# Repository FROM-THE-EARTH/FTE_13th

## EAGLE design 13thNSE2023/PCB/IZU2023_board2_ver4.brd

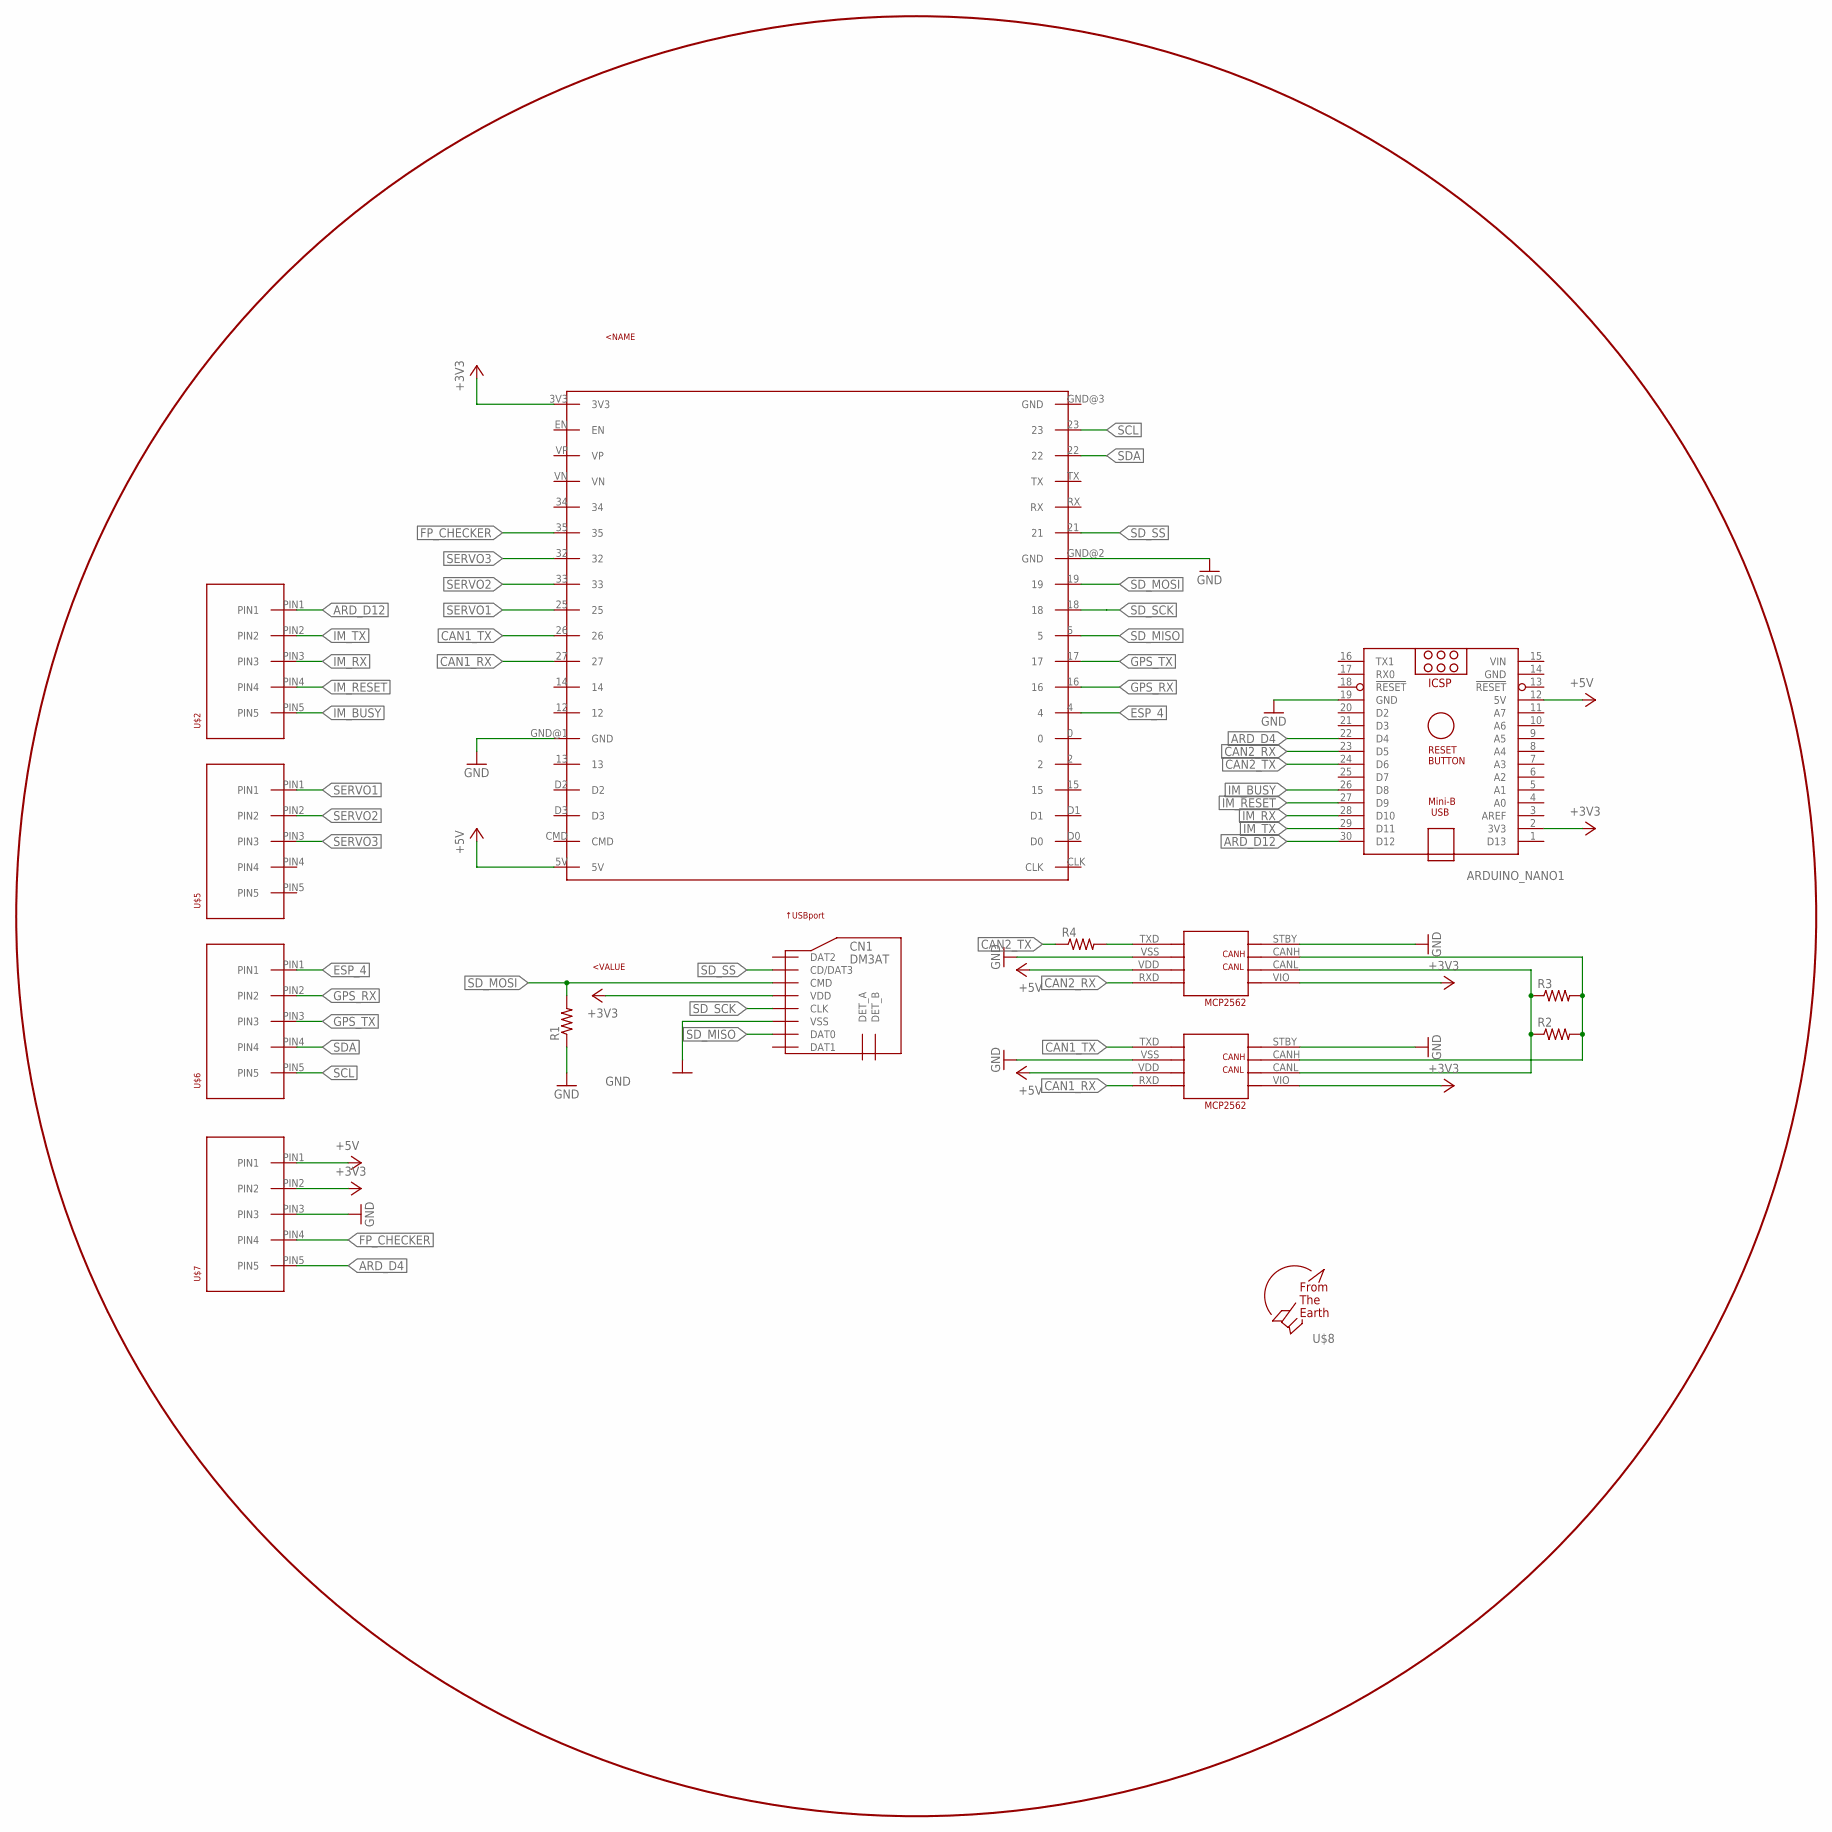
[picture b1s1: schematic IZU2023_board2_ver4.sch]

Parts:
ARDUINO_NANO1: ARDUINO_NANO
CN1: DM3AT
R1, R2, R3, R4: R-US_0204/7; 0204/7
U$1: ESP32-DEVKITC
U$2, U$5, U$6, U$7: 5PIN
U$3, U$4: MCP2562
U$8: F.T.E.LOGO; LOGO

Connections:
+3V3: ARDUINO_NANO1.2 (3V3), CN1.VDD, U$1.3V3, U$3.VIO, U$4.VIO, U$7.PIN2
+5V: ARDUINO_NANO1.12 (5V), U$1.5V, U$3.VDD, U$4.VDD, U$7.PIN1
ARD_D4: ARDUINO_NANO1.22 (D4), U$7.PIN5
ARD_D12: ARDUINO_NANO1.30 (D12), U$2.PIN1
CAN1_RX: U$1.27, U$3.RXD
CAN1_TX: U$1.26, U$3.TXD
CAN2_RX: ARDUINO_NANO1.23 (D5), U$4.RXD
CAN2_TX: ARDUINO_NANO1.24 (D6), R4.1
ESP_4: U$1.4, U$6.PIN1
FP_CHECKER: U$1.35, U$7.PIN4
GND: ARDUINO_NANO1.14 (GND), ARDUINO_NANO1.19 (GND), CN1.VSS, R1.1, U$1.GND@1 (GND), U$1.GND@2 (GND), U$3.STBY, U$3.VSS, U$4.STBY, U$4.VSS, U$7.PIN3
GPS_RX: U$1.16, U$6.PIN2
GPS_TX: U$1.17, U$6.PIN3
IM_BUSY: ARDUINO_NANO1.26 (D8), U$2.PIN5
IM_RESET: ARDUINO_NANO1.27 (D9), U$2.PIN4
IM_RX: ARDUINO_NANO1.28 (D10), U$2.PIN3
IM_TX: ARDUINO_NANO1.29 (D11), U$2.PIN2
unnamed: R4.2, U$4.TXD
unnamed: R2.1, R3.1, U$3.CANL, U$4.CANL
unnamed: R2.2, R3.2, U$3.CANH, U$4.CANH
SCL: U$1.23, U$6.PIN5
SDA: U$1.22, U$6.PIN4
SD_MISO: CN1.DAT0, U$1.5
SD_MOSI: CN1.CMD, R1.2, U$1.19
SD_SCK: CN1.CLK, U$1.18
SD_SS: CN1.CD/DAT3, U$1.21
SERVO1: U$1.25, U$5.PIN1
SERVO2: U$1.33, U$5.PIN2
SERVO3: U$1.32, U$5.PIN3
VIN: ARDUINO_NANO1.15 (VIN)

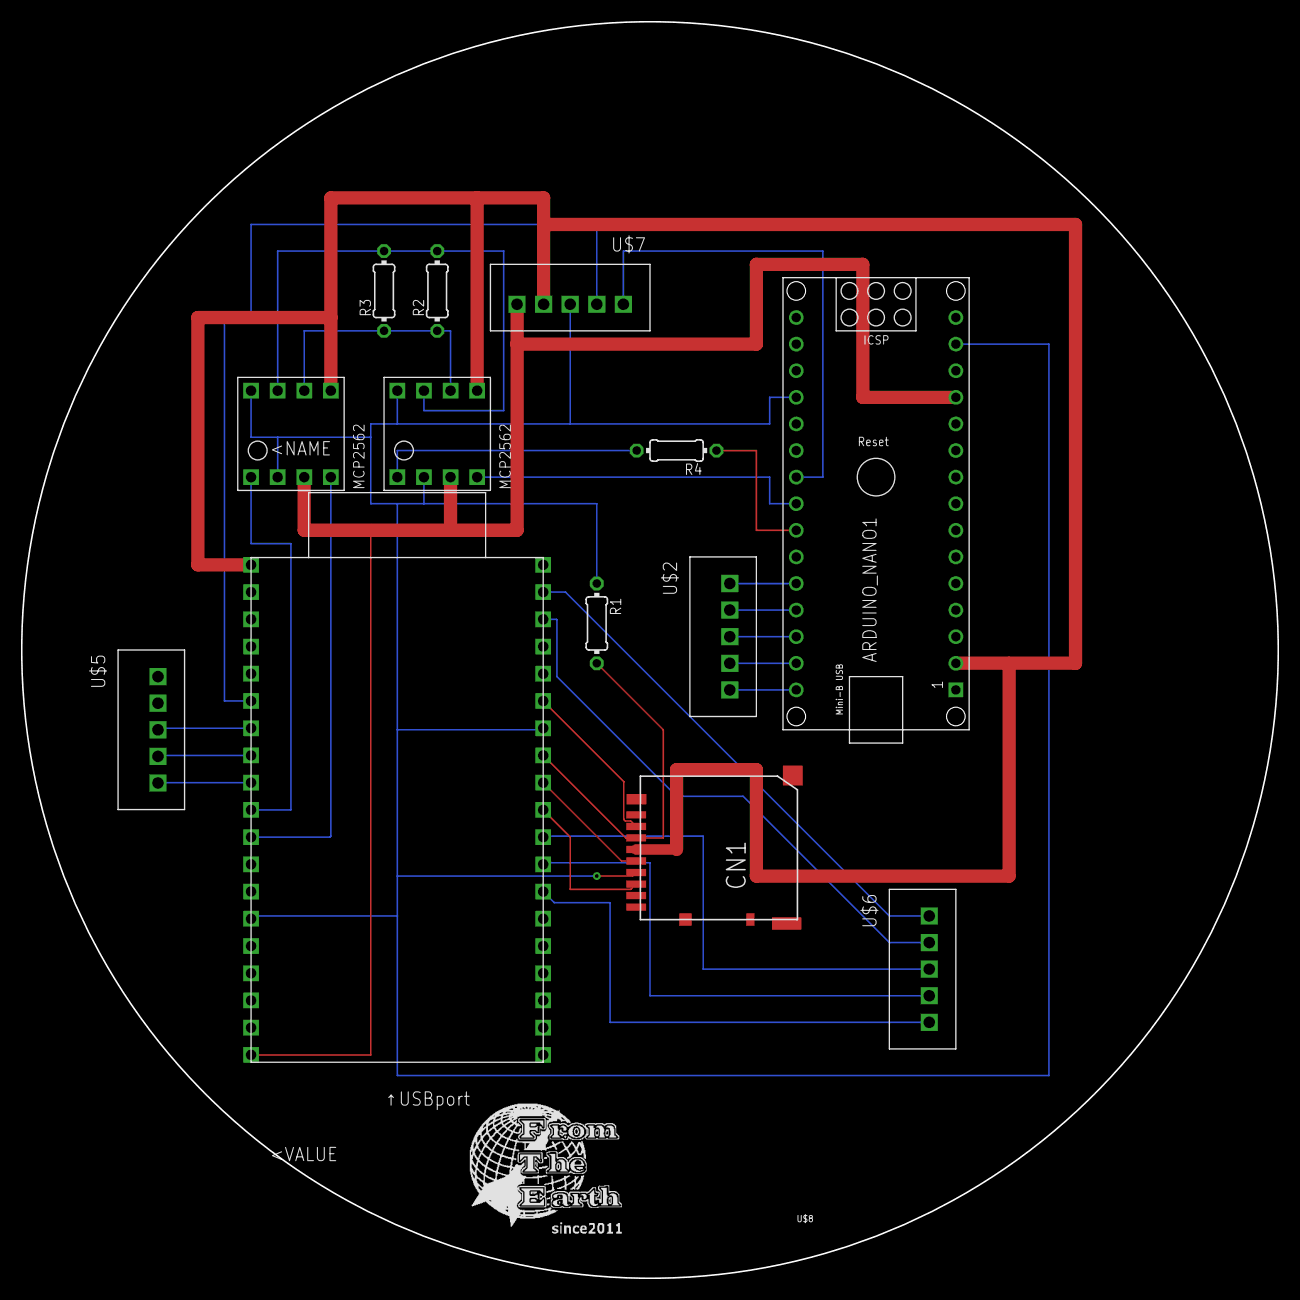
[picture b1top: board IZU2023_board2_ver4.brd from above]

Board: 2 copper layers, 120.0 x 120.0 mm, 14 parts (0 on the bottom side), 29 nets.

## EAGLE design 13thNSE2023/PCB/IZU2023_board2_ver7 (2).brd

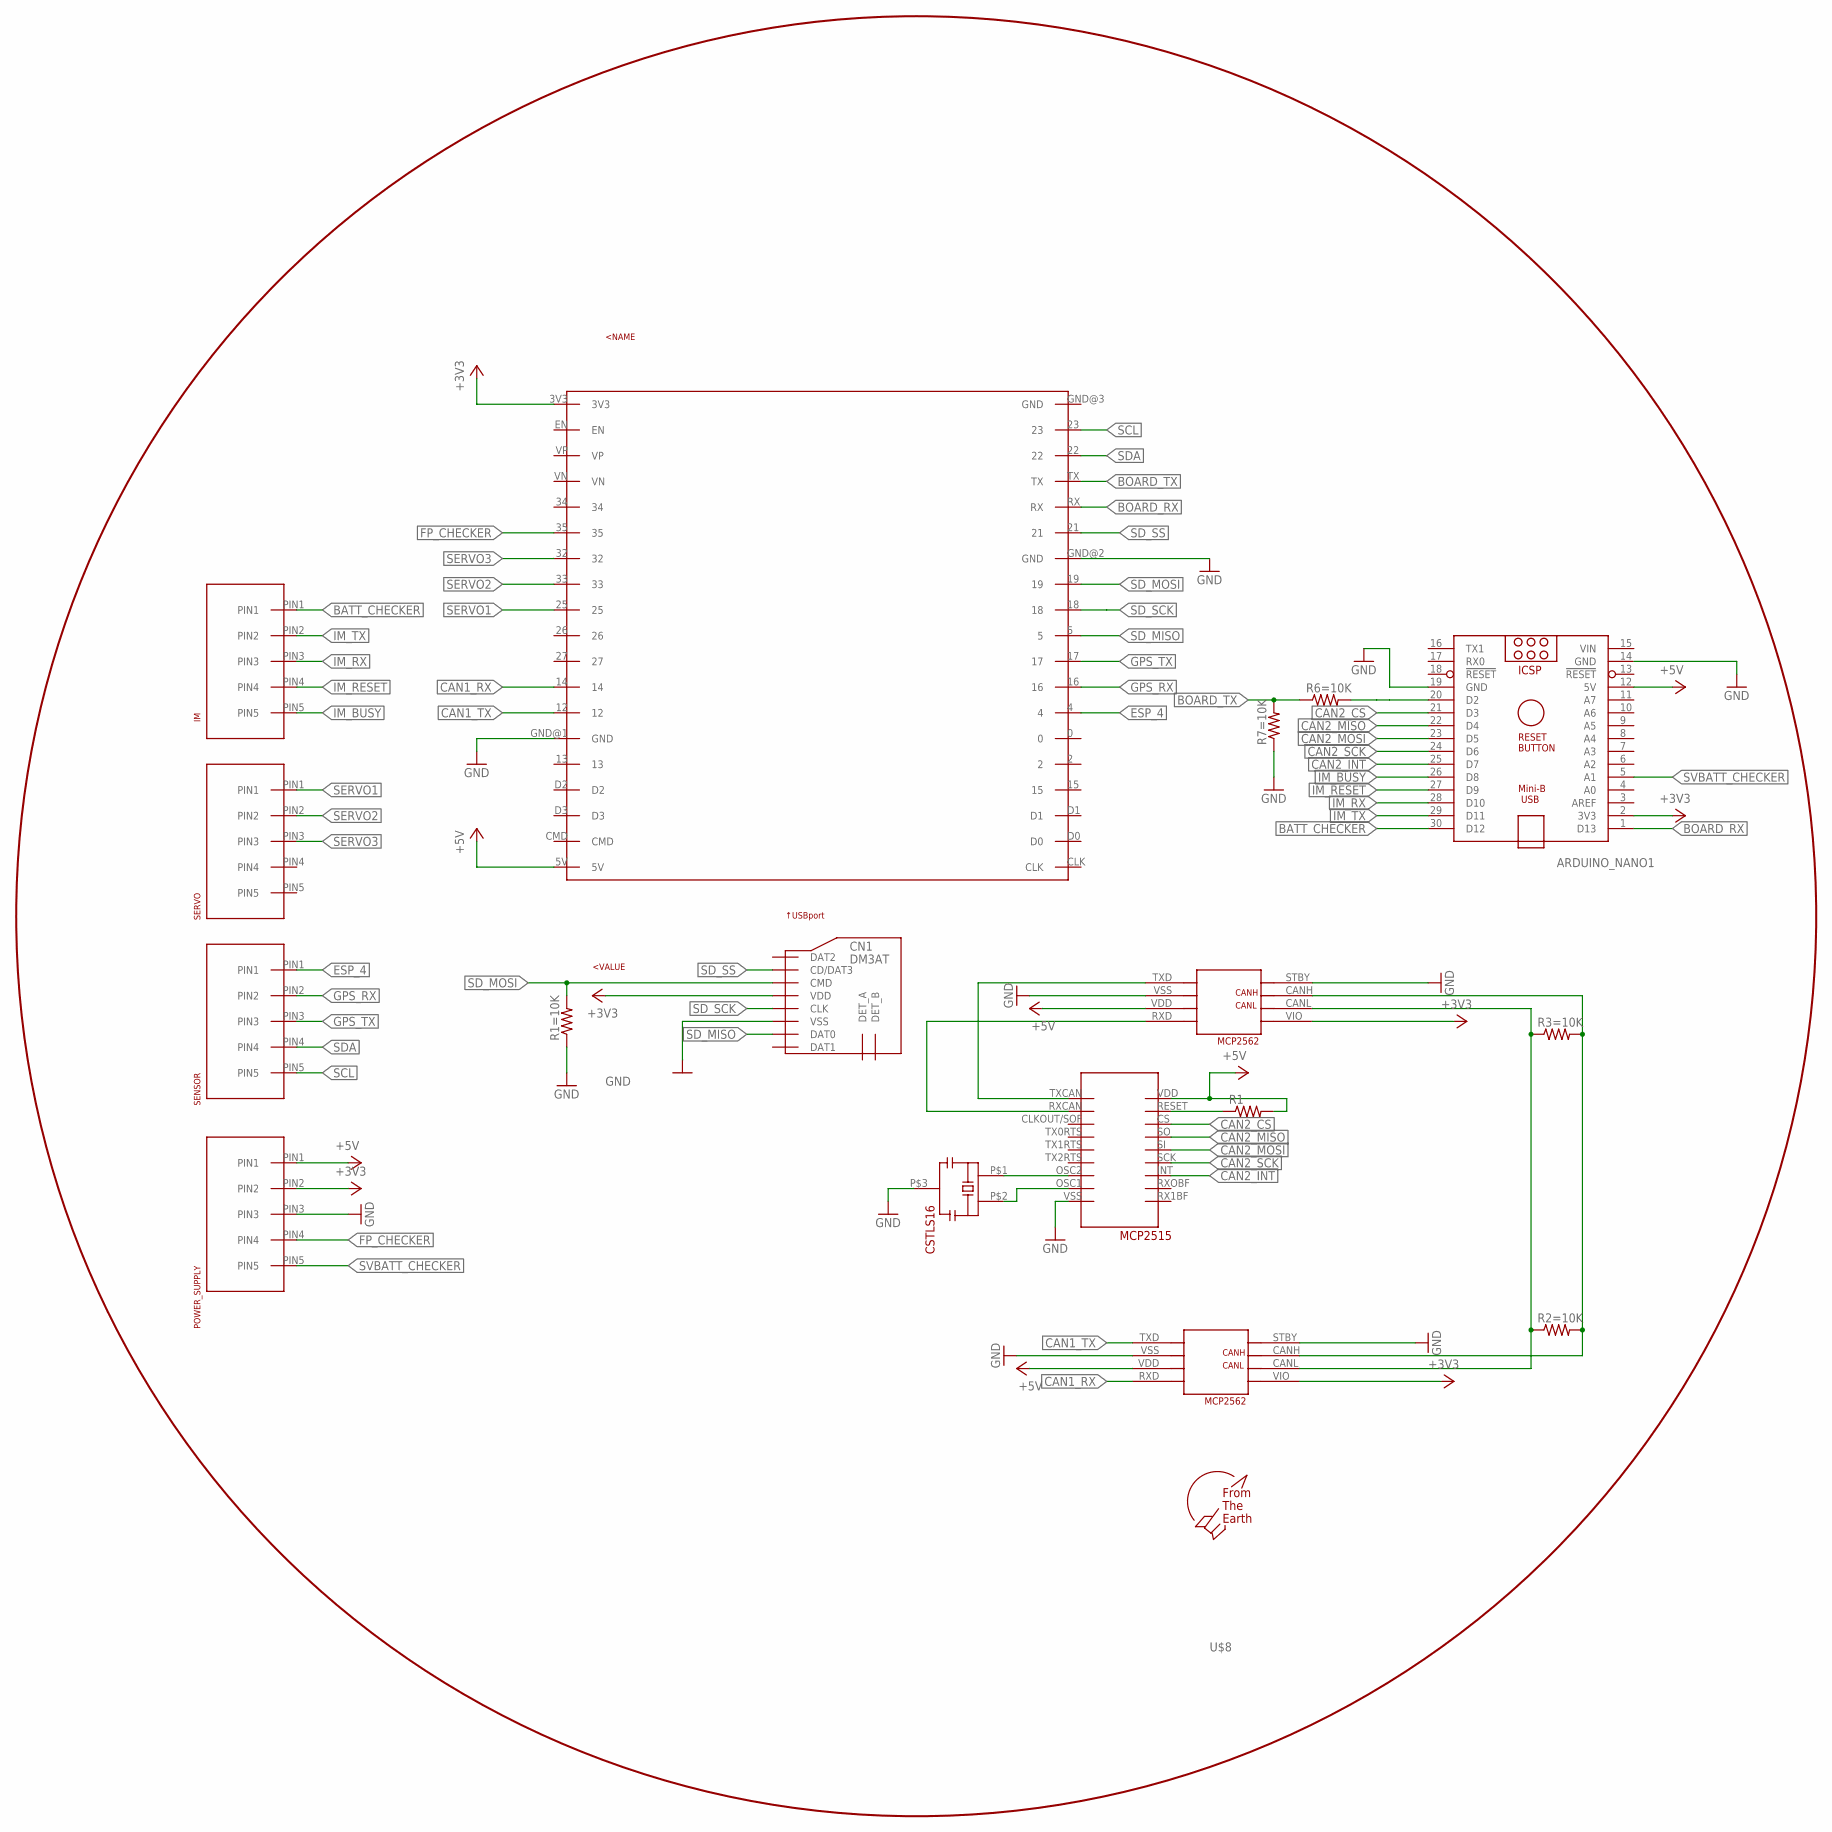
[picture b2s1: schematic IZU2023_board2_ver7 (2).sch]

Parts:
ARDUINO_NANO1: ARDUINO_NANO
CN1: DM3AT
IM: 5PIN
POWER_SUPPLY: 5PIN
R1, R1=10K, R2=10K, R3=10K, R6=10K, R7=10K: R-US_0204/7; 0204/7
SENSOR: 5PIN
SERVO: 5PIN
U$1: ESP32-DEVKITC
U$2: MCP2515
U$3, U$4: MCP2562
U$5: CSTLS16
U$8: F.T.E.LOGO; LOGO

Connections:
+3V3: ARDUINO_NANO1.2 (3V3), CN1.VDD, POWER_SUPPLY.PIN2, U$1.3V3, U$3.VIO, U$4.VIO
+5V: ARDUINO_NANO1.12 (5V), POWER_SUPPLY.PIN1, R1.2, U$1.5V, U$2.VDD, U$3.VDD, U$4.VDD
BATT_CHECKER: ARDUINO_NANO1.30 (D12), IM.PIN1
BOARD_RX: ARDUINO_NANO1.1 (D13), U$1.RX
BOARD_TX: R6=10K.1, R7=10K.2, U$1.TX
CAN1_RX: U$1.14, U$3.RXD
CAN1_TX: U$1.12, U$3.TXD
CAN2_CS: ARDUINO_NANO1.21 (D3), U$2.CS
CAN2_INT: ARDUINO_NANO1.25 (D7), U$2.INT
CAN2_MISO: ARDUINO_NANO1.22 (D4), U$2.SO
CAN2_MOSI: ARDUINO_NANO1.23 (D5), U$2.SI
CAN2_SCK: ARDUINO_NANO1.24 (D6), U$2.SCK
ESP_4: SENSOR.PIN1, U$1.4
FP_CHECKER: POWER_SUPPLY.PIN4, U$1.35
GND: ARDUINO_NANO1.14 (GND), ARDUINO_NANO1.19 (GND), CN1.VSS, POWER_SUPPLY.PIN3, R1=10K.1, R7=10K.1, U$1.GND@1 (GND), U$1.GND@2 (GND), U$2.VSS, U$3.STBY, U$3.VSS, U$4.STBY, U$4.VSS, U$5.P$3
GPS_RX: SENSOR.PIN2, U$1.16
GPS_TX: SENSOR.PIN3, U$1.17
IM_BUSY: ARDUINO_NANO1.26 (D8), IM.PIN5
IM_RESET: ARDUINO_NANO1.27 (D9), IM.PIN4
IM_RX: ARDUINO_NANO1.28 (D10), IM.PIN3
IM_TX: ARDUINO_NANO1.29 (D11), IM.PIN2
unnamed: U$2.TXCAN, U$4.TXD
unnamed: ARDUINO_NANO1.20 (D2), R6=10K.2
unnamed: R2=10K.1, R3=10K.1, U$3.CANL, U$4.CANL
unnamed: R2=10K.2, R3=10K.2, U$3.CANH, U$4.CANH
unnamed: U$2.RXCAN, U$4.RXD
unnamed: U$2.OSC2, U$5.P$1
unnamed: U$2.OSC1, U$5.P$2
unnamed: R1.1, U$2.RESET
SCL: SENSOR.PIN5, U$1.23
SDA: SENSOR.PIN4, U$1.22
SD_MISO: CN1.DAT0, U$1.5
SD_MOSI: CN1.CMD, R1=10K.2, U$1.19
SD_SCK: CN1.CLK, U$1.18
SD_SS: CN1.CD/DAT3, U$1.21
SERVO1: SERVO.PIN1, U$1.25
SERVO2: SERVO.PIN2, U$1.33
SERVO3: SERVO.PIN3, U$1.32
SVBATT_CHECKER: ARDUINO_NANO1.5 (A1), POWER_SUPPLY.PIN5
VIN: ARDUINO_NANO1.15 (VIN)

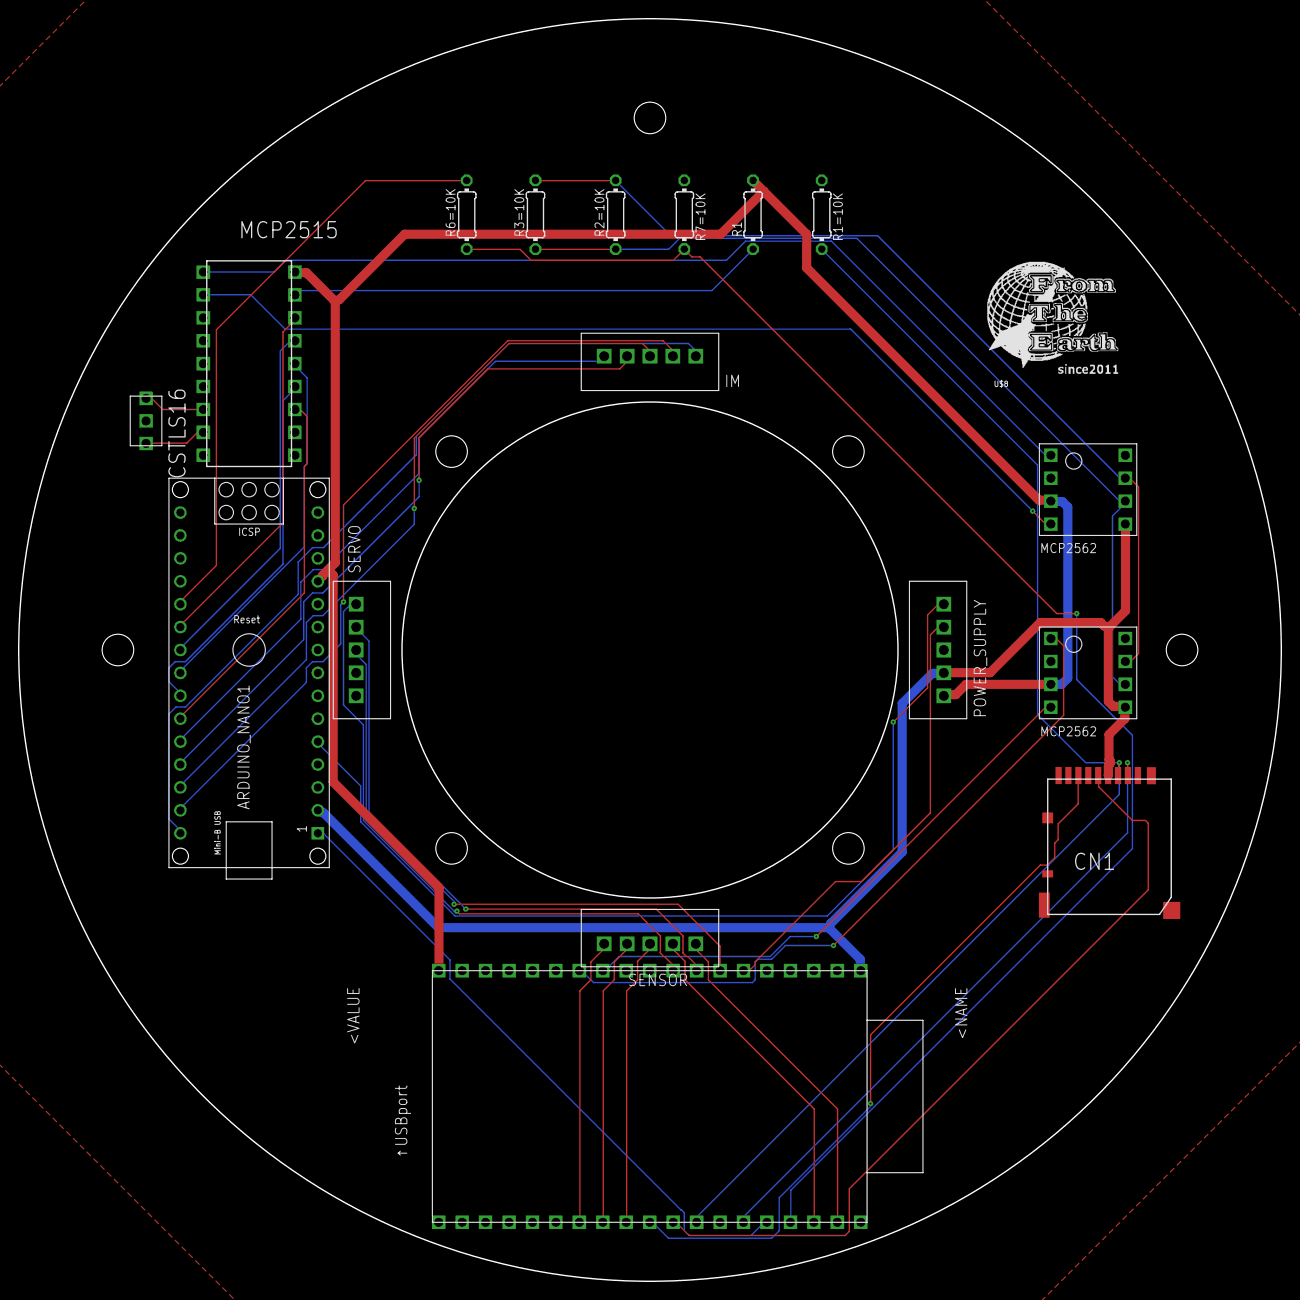
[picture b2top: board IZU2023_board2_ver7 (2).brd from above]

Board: 2 copper layers, 140.0 x 140.0 mm, 18 parts (0 on the bottom side), 39 nets.

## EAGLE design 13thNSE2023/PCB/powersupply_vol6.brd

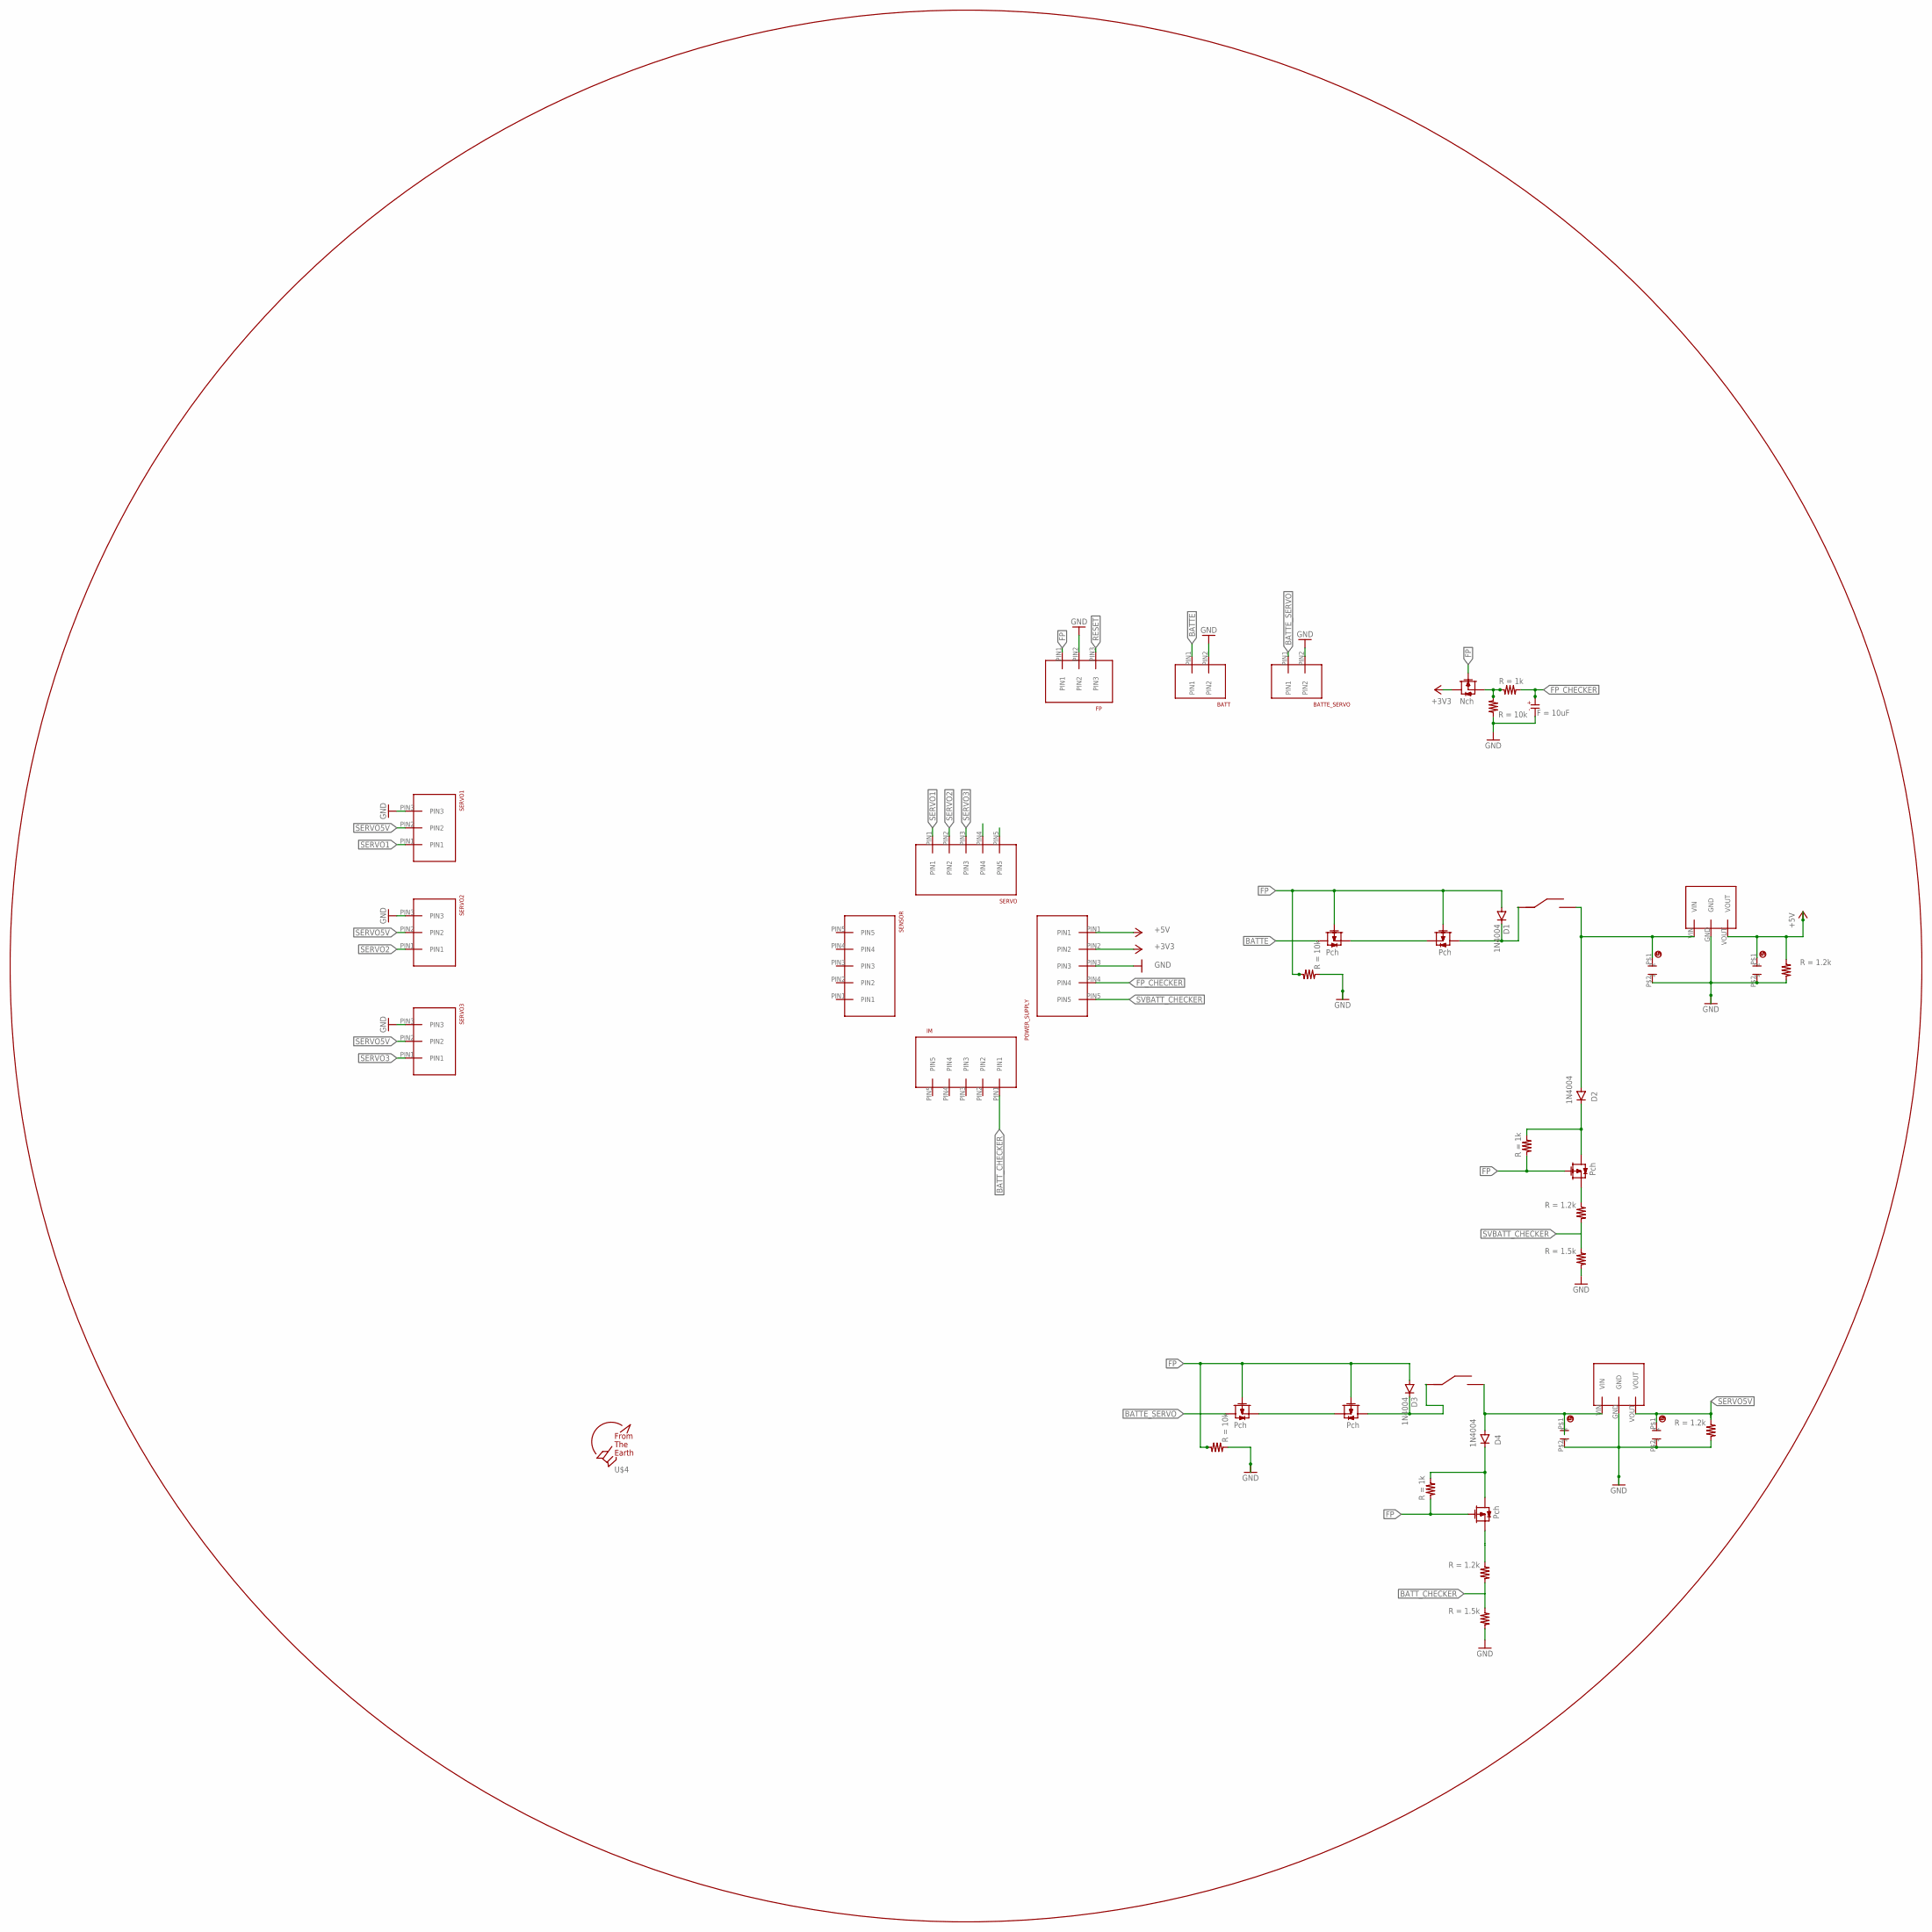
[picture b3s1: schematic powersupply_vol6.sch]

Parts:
BATT: 2PIN
BATTE_SERVO: 2PIN
C1: CAPACITOR-ELECTROLYTIC_1
CERAMIC_CAPACITOR3, CERAMIC_CAPACITOR4, CERAMIC_CAPACITOR5, CERAMIC_CAPACITOR6: CERAMIC_CAPACITOR
D1, D2, D3, D4: 1N4004; DO41-10
FP: 3PIN
IM: 5PIN
POWER_SUPPLY: 5PIN
R1, R4: 1.5k; REGISTER
R2, R3, R5, R6, R7, R8, R9, R10, R11, R12: RESISTER; REGISTER
SENSOR: 5PIN
SERVO: 5PIN
SERVO1, SERVO2, SERVO3: 3PIN
U$1, U$5, U$12, U$13, U$30, U$31: 2SJ681-PCH; 2SJ681
U$2, U$3: SLIDESWITCH
U$4: F.T.E.LOGO; LOGO
U$8: 2SK4017-NCH; 2SK4017
U$14, U$32: M78AR05-1

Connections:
+3V3: POWER_SUPPLY.PIN2, U$8.DRAIN
+5V: CERAMIC_CAPACITOR5.P$1 (1), POWER_SUPPLY.PIN1, R11.A, U$32.VOUT
BATTE: BATT.PIN1, U$30.DRAIN
BATTE_SERVO: BATTE_SERVO.PIN1, U$13.DRAIN
BATT_CHECKER: IM.PIN1, R1.A, R3.B
FP: D1.A, D3.A, FP.PIN1, R2.B, R5.B, R7.B, R8.B, U$1.GATE, U$5.GATE, U$8.GATE, U$12.GATE, U$13.GATE, U$30.GATE, U$31.GATE
FP_CHECKER: C1.KS, POWER_SUPPLY.PIN4, R10.A
GND: BATT.PIN2, BATTE_SERVO.PIN2, C1.AN, CERAMIC_CAPACITOR3.P$2 (2), CERAMIC_CAPACITOR4.P$2 (2), CERAMIC_CAPACITOR5.P$2 (2), CERAMIC_CAPACITOR6.P$2 (2), FP.PIN2, POWER_SUPPLY.PIN3, R1.B, R2.A, R4.B, R5.A, R9.A, R11.B, R12.B, SERVO1.PIN3, SERVO2.PIN3, SERVO3.PIN3, U$14.GND, U$32.GND
unnamed: D2.C, R7.A, U$1.DRAIN
unnamed: U$12.SOURCE, U$13.SOURCE
unnamed: R6.A, U$1.SOURCE
unnamed: D4.C, R8.A, U$5.DRAIN
unnamed: R9.B, R10.B, U$8.SOURCE
unnamed: CERAMIC_CAPACITOR4.P$1 (1), D4.A, U$3.C, U$14.VIN
unnamed: R3.A, U$5.SOURCE
unnamed: D1.C, U$2.A, U$31.DRAIN
unnamed: D3.C, U$3.A, U$12.DRAIN
unnamed: U$30.SOURCE, U$31.SOURCE
unnamed: CERAMIC_CAPACITOR6.P$1 (1), D2.A, U$2.C, U$32.VIN
RESET: FP.PIN3
SERVO1: SERVO.PIN1, SERVO1.PIN1
SERVO2: SERVO.PIN2, SERVO2.PIN1
SERVO3: SERVO.PIN3, SERVO3.PIN1
SERVO5V: CERAMIC_CAPACITOR3.P$1 (1), R12.A, SERVO1.PIN2, SERVO2.PIN2, SERVO3.PIN2, U$14.VOUT
SVBATT_CHECKER: POWER_SUPPLY.PIN5, R4.A, R6.B

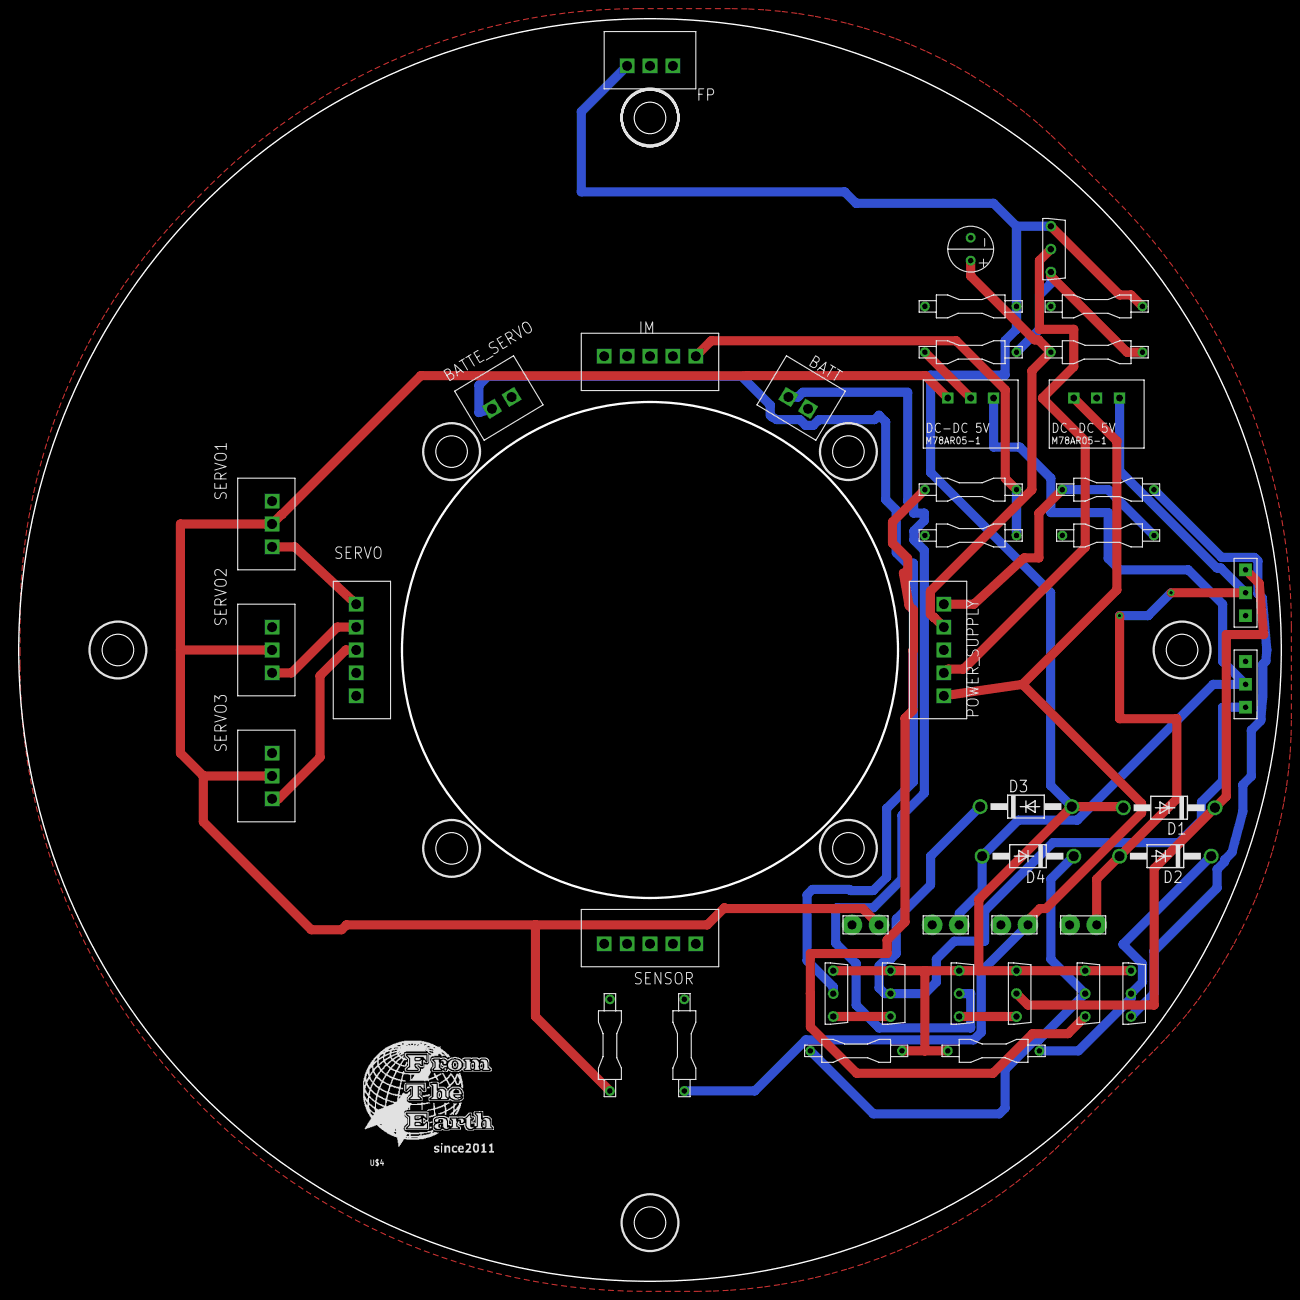
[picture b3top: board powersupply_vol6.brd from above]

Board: 2 copper layers, 140.0 x 140.0 mm, 43 parts (0 on the bottom side), 24 nets.

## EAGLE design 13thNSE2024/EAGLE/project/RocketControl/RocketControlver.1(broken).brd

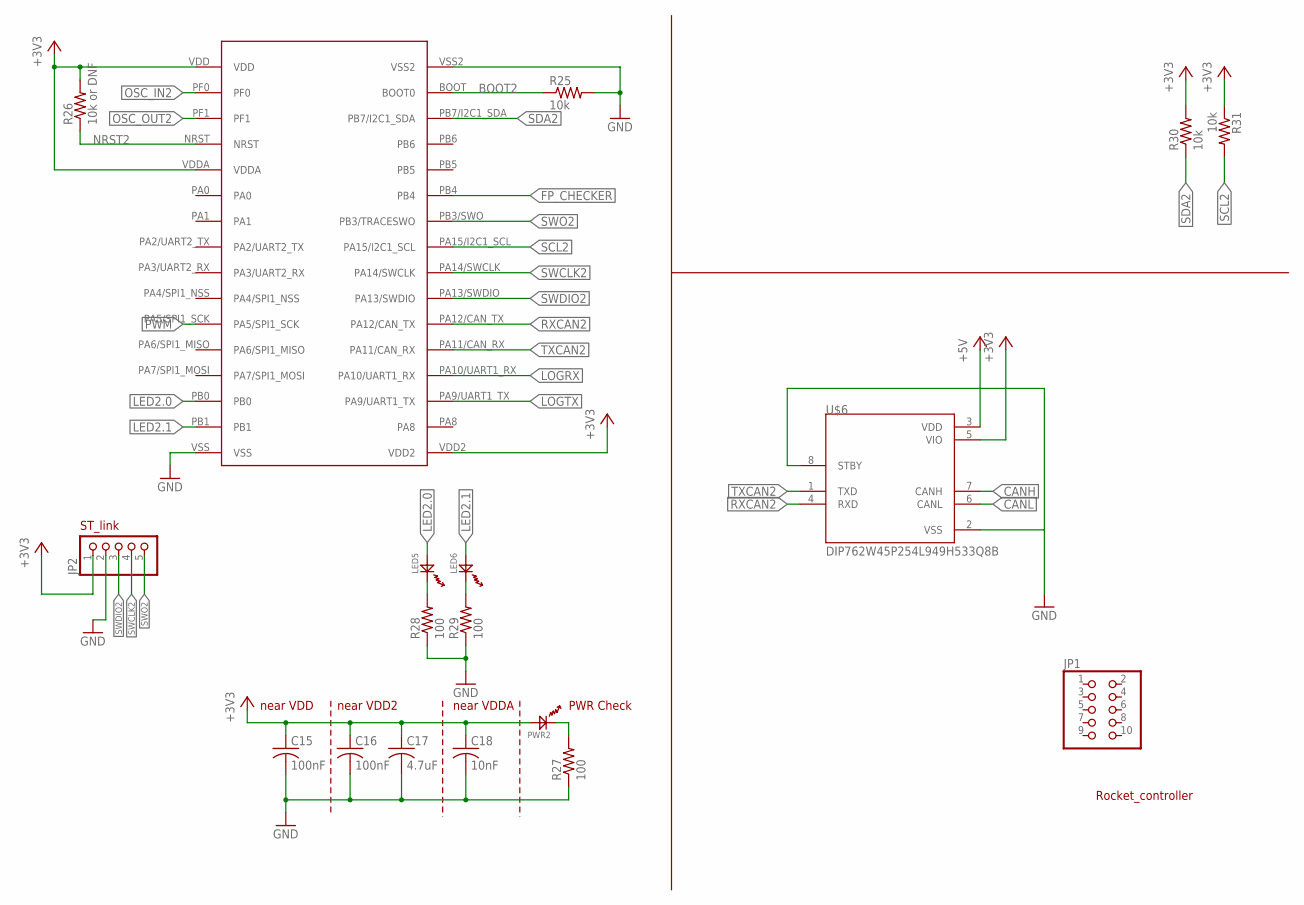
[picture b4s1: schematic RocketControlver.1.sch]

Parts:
C15, C16: 100nF; C1608
C17: 4.7uF; C1608
C18: 10nF; C1608
JP1: PINHD-2X5/90; 2X05/90
JP2: PINHD-1X5/90; 1X05/90
LED5, LED6: OSXX1608C1A
PWR2: OSXX1608C1A
R25, R30, R31: 10k; R0603
R26: 10k or DNF; R0603
R27, R28, R29: 100; R0603
U$1: STM32F303K8
U$6: DIP762W45P254L949H533Q8B

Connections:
+3V3: C15.1, C16.1, C17.1, C18.1, JP2.1, PWR2.AN, R26.2, R30.2, R31.1, U$1.VDD, U$1.VDD2, U$1.VDDA, U$6.5 (VIO)
+5V: U$6.3 (VDD)
BOOT2: R25.1, U$1.BOOT (BOOT0)
CANH: U$6.7 (CANH)
CANL: U$6.6 (CANL)
FP_CHECKER: U$1.PB4
GND: C15.2, C16.2, C17.2, C18.2, JP2.2, R25.2, R27.1, R28.1, R29.1, U$1.VSS, U$1.VSS2, U$6.2 (VSS), U$6.8 (STBY)
LED2.0: LED5.AN, U$1.PB0
LED2.1: LED6.AN, U$1.PB1
LOGRX: U$1.PA10/UART1_RX
LOGTX: U$1.PA9/UART1_TX
unnamed: PWR2.CT, R27.2
unnamed: LED5.CT, R28.2
unnamed: LED6.CT, R29.2
NRST2: R26.1, U$1.NRST
OSC_IN2: U$1.PF0
OSC_OUT2: U$1.PF1
PWM: U$1.PA5/SPI1_SCK
RXCAN2: U$1.PA12/CAN_TX, U$6.4 (RXD)
SCL2: R31.2, U$1.PA15/I2C1_SCL
SDA2: R30.1, U$1.PB7/I2C1_SDA
SWCLK2: JP2.4, U$1.PA14/SWCLK
SWDIO2: JP2.3, U$1.PA13/SWDIO
SWO2: JP2.5, U$1.PB3/SWO (PB3/TRACESWO)
TXCAN2: U$1.PA11/CAN_RX, U$6.1 (TXD)

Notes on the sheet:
near VDD
near VDD2
near VDDA
PWR Check
Rocket_controller
ST_link

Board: 2 copper layers, 18 parts (0 on the bottom side), 16 nets, no tracks yet.
